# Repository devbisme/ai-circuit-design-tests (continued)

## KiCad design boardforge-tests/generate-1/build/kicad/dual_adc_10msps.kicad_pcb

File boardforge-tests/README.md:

# boardforge — tests

## Tool under test

[boardforge](https://github.com/devbisme/boardforge) turns a SKiDL circuit into a routed,
manufacturable KiCad board, headless. It has two parts:

- **A Python CLI, `boardforge`.** A project is a directory with a SKiDL file and a
  `boardforge.toml`. The CLI runs:
  - The physical pipeline (`run`, or one stage at a time): C1 `sch` (SKiDL → netlist →
    labels-only KiCad schematic via schematizer, SKiDL and KiCad ERC, netlist parity), C2
    `board`, C3 `place` (anchors, regions, FPGA/MCU pin swapping, compaction, a routability
    estimate), C4 `route` (Freerouting, then a built-in A*), C5 `check` (DRC, geometry
    checks, vendored kicad-happy 2.3.1 analyzers, thermal), C6 `fab` (JLCPCB Gerbers, BOM,
    CPL, schematic PDF, renders).
  - The B4 review gate (`review`): `constraints.json` checked against the design with
    ngspice path testbenches, rail-current budgets, datasheet absolute-max and power-pin
    checks, footprint-vs-datasheet package checks and a BOM diff.
  - A datasheet cache (`datasheets status | sync | add | check | show | publish | paths`),
    plus `render`, `status` and `doctor`.
- **A Claude Code plugin** (adapted from skidl-skills). `/new-circuit` drives seven phases:
  requirements (interview) → architecture and `constraints.json` (`circuit-architect`) →
  sourcing (`part-sourcer`) → datasheet extractions (`datasheet-librarian`) → SKiDL code
  (`skidl-coder`, or block coders plus `skidl-assembler`) → review (`erc-reviewer`) → board
  (the driver, using the CLI). There is an approval gate after each phase. Other skills:
  `design-review`, `erc-rules`, `find-part` (pcbparts MCP, with `skidl-part-search` as the
  fallback). Four hooks guard Bash calls, check written files, and print status at session
  start and stop.

The design-creating parts are `/new-circuit`, its agents, and `boardforge run`. The review
parts (`boardforge review`, `/design-review`, the C5 checks) all work on a boardforge SKiDL
project, not on an arbitrary KiCad design. So it is tested as a **generator** only.
Installation is described in [`setup.md`](setup.md).

- **Version:** boardforge 0.1.0 (PyPI). The plugin is 0.1.0 at commit 437b70d (2026-10-16),
  installed as `boardforge@devbisme-skills`.
- **Model:** Claude Opus 5.5 for the driver and the opus agents; Claude Sonnet 5.5 for
  `part-sourcer` (both set by the agents' frontmatter).
- **Claude Code version:** v2.1.302 (v2.1.301 at setup time).
- **Backend:** KiCad 10.0.4 (`~/bin/kicad10-root`: `kicad-cli` and the bundled Python 3.11
  `pcbnew`), SKiDL 3.0.0, schematizer 0.2.0, Freerouting 2.4.1, ngspice 44.2.

## Why this tool

<!-- TODO (author): drafted by Claude from the tool's description; replace with your own reasons. -->
- It is the successor to [skidl-skills](../skidl-skills-tests/), and it moves everything
  deterministic into a CLI: running the design, ERC, review gates, placement, routing and
  fab outputs. Agents only make decisions and call commands. The test is whether that
  lowers cost and gets further than skidl-skills, which stopped at a netlist.
- It covers the whole flow from prompt to fab files, with numeric review gates
  (`constraints.json` checked with ngspice) that the other generators don't have.

## Runs

| Run | What it tests | Prompts | Outcome | Equiv. API cost | Time |
|---|---|---|---|---|---|
| [`generate-1`](generate-1/) | A **full design** from the dual-ADC requirements | 1 ([`design_prompt.txt`](generate-1/design_prompt.txt)); no phase-gate approvals were needed (the prompt says not to pause) | 9-block SKiDL design → routed 4-layer 100 × 80 mm board, 239 parts. ERC 0 errors, netlist parity 217/217, review gate PASS, DRC 0 errors, release gate PASS. The C6 CPL dropped 80 parts (boardforge bug), fixed by hand | $23.89 | ~2 h 40 min wall clock (~8 min of it waiting out a session limit) |

### generate-1: full design

The prompt is [`design_prompt.txt`](generate-1/design_prompt.txt), identical to the one used
for the other tools' design runs (the dual-ADC prompt with the KiCad 10 path line).

Prompts, in sequence in one session:

```
create the design described in design-prompt.txt.
```

Claude invoked `/new-circuit` itself. Because the prompt says to choose options and not pause,
the driver ran phase 1 (requirements) without asking anything. Every requirement the prompt
didn't state is tagged `(driver)` in `SPEC.md`: 1 MΩ input, ±30 V protection, 1 MHz
passband, 4 layers, JLCPCB at qty 5. Each later approval gate was approved automatically.
One API session limit killed the datasheet agent partway through. The harness's "limit has
reset" message restarted the session, and the agent was resumed with its work intact.

Quick look:

- **Design:**
  - Signal path: BNC → 1 MΩ attenuator with a trimmer for probe compensation → BAV199
    clamp → OPA2810 buffer and two Sallen-Key stages → THS4551 FDA (MFB stage) → RC →
    ADS5231 (dual simultaneous 12-bit). The anti-alias filter has 7 poles: −80.9 dB at
    5 MHz nominal, −78.7 dB Monte-Carlo worst case (requirement ≥ 72 dB at fs/2).
  - Capture and link: XC6SLX9 Spartan-6 with a 16 MB W9812G6KH SDRAM (0.42 s at full rate)
    → FT232H sync FIFO → USB-C (USB 2.0 HS). W25Q32 config flash, JTAG and TRIG headers.
  - Power: 0.43 A worst case, so standard USB 2.0 power is enough; USB-C kept anyway.
    TLV62569 buck (3.3 V), TLV757 (1.2 V), LP5907 (3.3 V analog), LM27762 (±4 V).
  - 9 blocks (afe_channel instantiated twice), so the modular coding mode was used: 5 block
    work orders, then `skidl-assembler`.
- **Gates:**
  - Assembly first gave KiCad ERC 4 errors (missing power flags, J501 shield pin) and a BOM
    FAIL: none of the block coders set `LCSC` fields, though the rules require them.
  - One fix pass followed. It added the LCSC fields, 2 flags, the shield pin, and an R705
    pull-up for the LM27762 PGOOD pin; Claude added R705 to the BOM.
  - After that: SKiDL and KiCad ERC 0 errors, parity 217/217, `boardforge review` 43 PASS /
    0 FAIL / 13 NOT CHECKED, BOM PASS. `erc-reviewer` passed the design with 3 MEDIUM
    findings.
- **PCB (`boardforge run --from c2`):** 100 × 80 mm, 4 layers (In1 GND, In2 +3V3, GND pours
  on both outer layers).
  - Claude wrote the floorplan: 15 anchors, with the BNCs on the left edge, USB-C on the
    right, and the AFE → ADC → FPGA → FT232H chain left to right. One extra placement
    round anchored the USB ESD part U501, which C3 had put mid-board.
  - Routing took 11.4 min. Freerouting left 2 unrouted and 64 DRC errors; the A* router
    cleaned them up to 0/0.
  - DRC: 0 errors, 50 warnings (silkscreen 36, dangling stubs 9, hole-to-hole 5). Release
    gate PASS 12/12. 714 vias.
- **Not ready for fab:**
  - ADS5231 AVDD/VDRV abs-max is briefly exceeded at power-up (review W2; the fix is a
    one-net change, but it alters a block's signature). FT232H VREGIN sits at its 3.3 V
    minimum (W3).
  - ADS5231: single source, 152 in stock.
  - Facts that could not be verified:
    - The 12 MHz crystal has no datasheet.
    - The oscillator's jitter is unspecified.
    - The SDRAM facts come from the W9812G6JH datasheet.
  - The custom BNC and trimmer footprints have not been checked against their drawings.
  - No FPGA gateware, FT232H EEPROM image or host software.
- **boardforge problems found:**
  - **C6 CPL drops parts.**
    - Cause: `kicad-cli sch export bom` groups designators into ranges (`C1001-C1022`),
      and `_expand_designators` in the vendored `translate_bom_pnp.py` doesn't expand
      them. The CPL's BOM filter therefore silently dropped 80 of 239 parts.
    - Workaround: Claude regenerated the BOM and CPL in `build/fab/` with the ranges
      expanded, using boardforge's own adapter.
    - Fix: pass `--ref-range-delimiter ""` to the export call in `physical.py`.
    - Re-running `boardforge fab` brings the bug back.
  - **Review gate can't check a custom dual op-amp.** The SPICE path checks (GAIN and
    ALIAS, both HARD) report NOT CHECKED because boardforge can't map the OPA2810
    symbol's pin names (`VIN1+`, `VO1`) to op-amp roles, and `[review.models]` takes only
    one pin map per part. `erc-reviewer` re-ran the checker with the names mapped: 12/12
    pass (`build/reports/spice_patched/`).
  - **Stale stock data.** The `stock-check.py` mirror reported 7 in stock for the W25Q32;
    live stock was 12,414. The sourcer used pcbparts instead.
  - **Run-to-run netlist differences.** The symbol definitions of multi-unit parts list
    their pins in a different order on each run, so `diff` reports the netlists as
    different even though components and nets are identical.
  - **Other C4/C5 warnings:**
    - C4: fanout failed for 2 FPGA GND pads, and the copper cleanup was skipped because it
      would have disconnected 3 items.
    - C5: rail-current analysis doesn't recognise the LM27762's ±4 V outputs.
    - C6: 12 parts have CPL rotation offsets from an unverified table.
    - KiCad ERC: 258 `lib_symbol_mismatch` warnings.
  - **Agent behaviour:**
    - Block coders used two different conventions for power flags (`drive = POWER` vs
      `PWR_FLAG`), which caused 2 of the ERC errors.
    - The architect and sourcer returned receipts over the 10-line limit.

## Layout

```
boardforge-tests/
├── README.md                   <- this file
├── setup.md                    <- how boardforge was installed and configured
└── generate-1/                 <- run 1: full design from the dual-ADC prompt
    ├── .claude/settings.local.json  <- enables the plugin for this directory only
    ├── design_prompt.txt       <- the design prompt
    ├── claude_transcript.txt   <- session transcript (/export)
    ├── claude_cost.txt         <- token usage and equivalent API cost
    ├── session_cost.py         <- script that produces claude_cost.txt
    ├── executive_summary.md    <- what was done, results, risks
    ├── SPEC.md                 <- requirements, user vs. driver provenance
    ├── design_state.json       <- pipeline state written by the /new-circuit driver
    ├── handoffs/               <- one handoff per phase (and per block in 05_blocks/)
    ├── architecture/           <- block diagram, net plan, IC selection, risks, AFE SPICE deck
    ├── constraints.json        <- numeric review-gate constraints (ac_gain, rail_current)
    ├── sourcing/               <- sourced_bom.md / .csv
    ├── datasheets/             <- PDFs, extracted/*.json, *_SUMMARY.md
    ├── symbols/, footprints/   <- custom ADS5231/OPA2810 symbols, BNC and trimmer footprints
    ├── circuits/dual_adc_10msps/  <- SKiDL package: 9 block files + __main__.py
    ├── boardforge.toml         <- design, board and floorplan settings
    ├── review_report.md        <- erc-reviewer's phase 6 report
    └── build/                  <- kicad/ (schematic, board), reports/, renders/, fab/
```

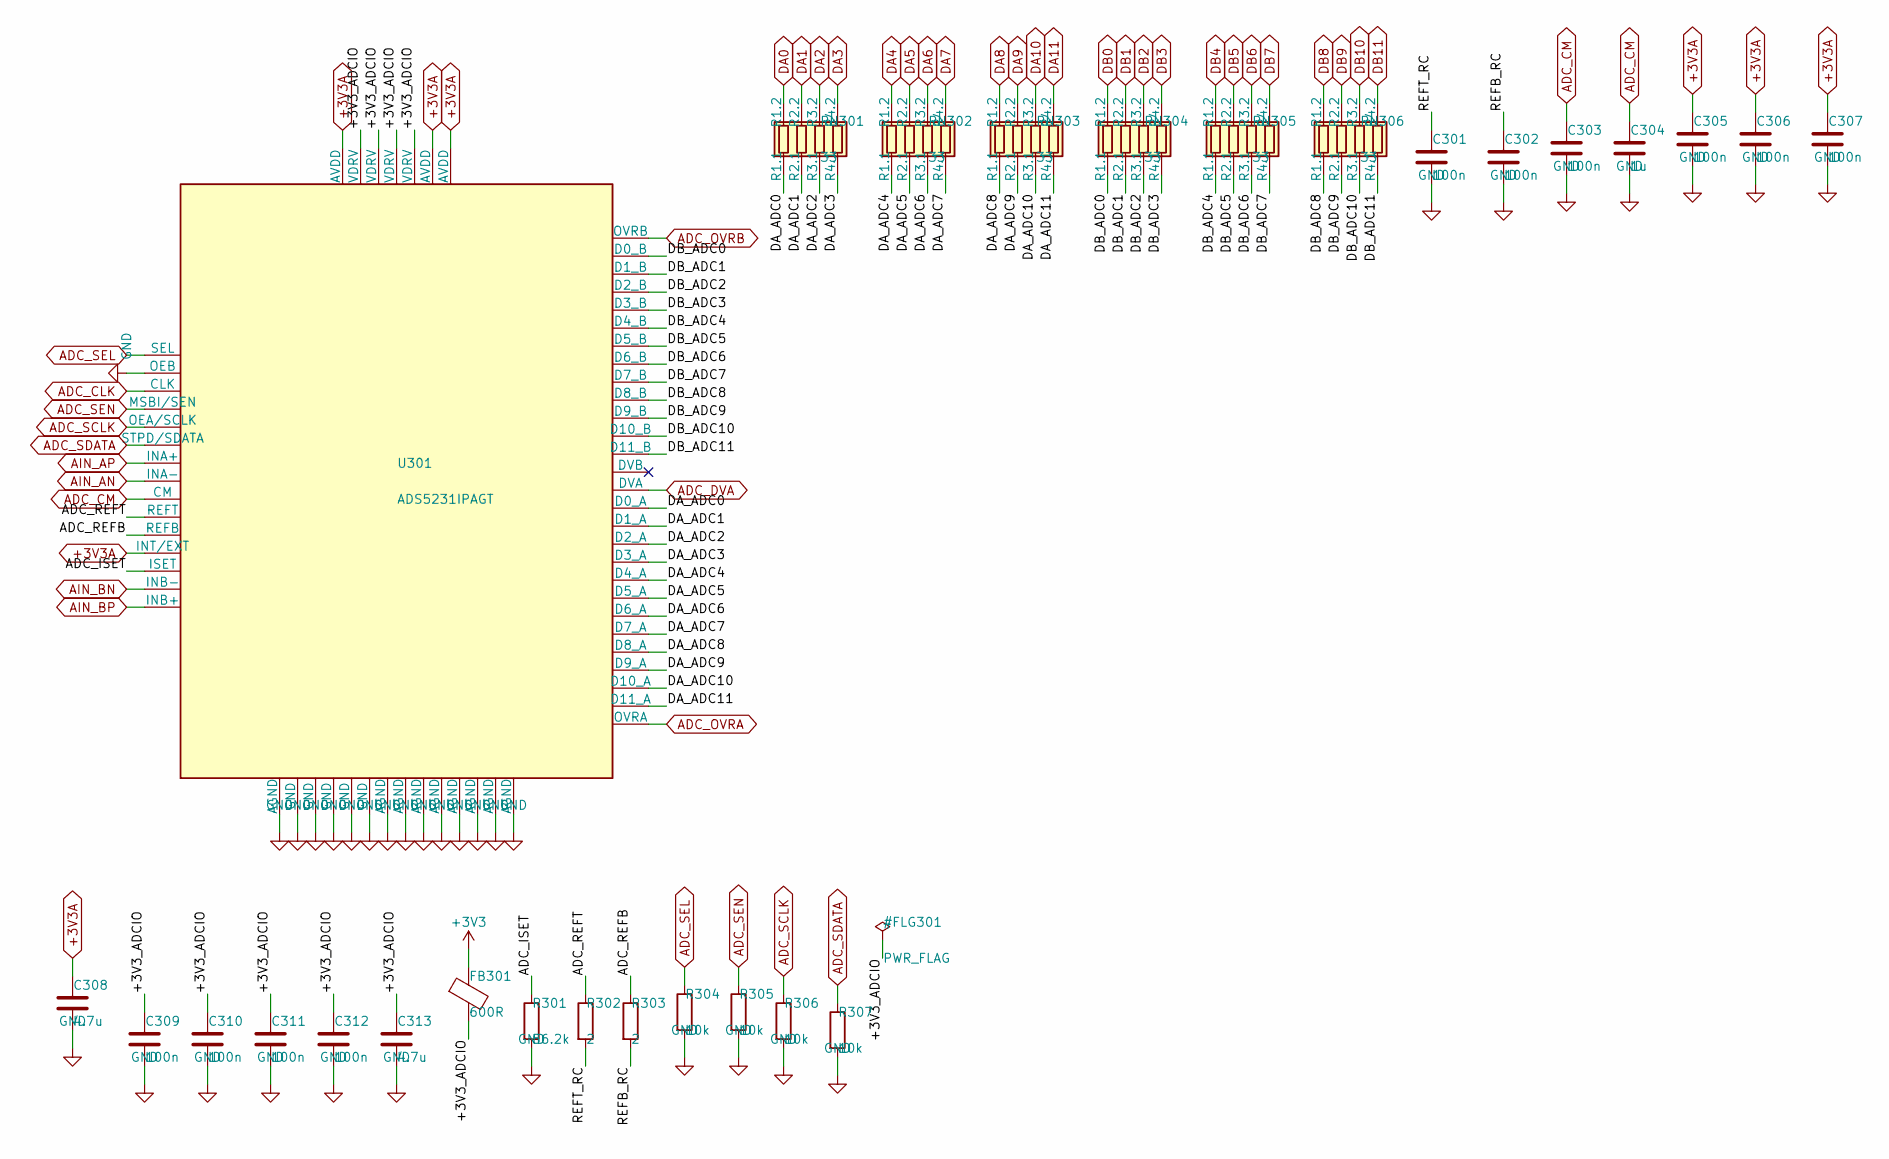
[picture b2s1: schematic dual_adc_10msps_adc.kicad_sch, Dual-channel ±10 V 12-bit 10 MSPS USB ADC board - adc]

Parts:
C301, C302, C303, C305, C306, C307, C309, C310, C311, C312: 100n; C_0402_1005Metric; MPN CL05B104KB54PNC; LCSC C307331
C304: 1u; C_0402_1005Metric; MPN CL05A105KA5NQNC; LCSC C52923
C308, C313: 4.7u; C_0603_1608Metric; MPN CL10A475KO8NNNC; LCSC C19666
FB301: 600R; L_0603_1608Metric; MPN BLM18KG601SN1D; LCSC C85833
R301: 56.2k; R_0402_1005Metric; MPN FRC0402F5622TS; LCSC C5126096
R302, R303: 2; R_0402_1005Metric; MPN FRC0402F2R00TS; LCSC C2998051
R304, R305, R306, R307: 10k; R_0402_1005Metric; MPN 0402WGF1002TCE; LCSC C25744
RN301, RN302, RN303, RN304, RN305, RN306: 33; R_Array_Convex_4x0402; MPN 4D02WGJ0330TCE; LCSC C25501
U301: ADS5231IPAGT; TQFP-64_10x10mm_P0.5mm; MPN ADS5231IPAGT; LCSC C2670079

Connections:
+3V3: FB301.1; also elsewhere on the board
+3V3A: C305.1, C306.1, C307.1, C308.1, U301.3 (AVDD), U301.46 (AVDD), U301.56 (INT/EXT), U301.57 (AVDD); also elsewhere on the board
/adc/+3V3_ADCIO: C309.1, C310.1, C311.1, C312.1, C313.1, FB301.2, U301.5 (VDRV), U301.8 (VDRV), U301.40 (VDRV), U301.43 (VDRV)
/adc/ADC_ISET: R301.1, U301.60 (ISET)
/adc/ADC_REFB: R303.1, U301.54 (REFB)
/adc/ADC_REFT: R302.1, U301.53 (REFT)
/adc/DA_ADC0: RN301.1 (R1.1), U301.27 (D0_A)
/adc/DA_ADC1: RN301.2 (R2.1), U301.28 (D1_A)
/adc/DA_ADC2: RN301.3 (R3.1), U301.29 (D2_A)
/adc/DA_ADC3: RN301.4 (R4.1), U301.30 (D3_A)
/adc/DA_ADC4: RN302.1 (R1.1), U301.31 (D4_A)
/adc/DA_ADC5: RN302.2 (R2.1), U301.32 (D5_A)
/adc/DA_ADC6: RN302.3 (R3.1), U301.33 (D6_A)
/adc/DA_ADC7: RN302.4 (R4.1), U301.34 (D7_A)
/adc/DA_ADC8: RN303.1 (R1.1), U301.35 (D8_A)
/adc/DA_ADC9: RN303.2 (R2.1), U301.36 (D9_A)
/adc/DA_ADC10: RN303.3 (R3.1), U301.37 (D10_A)
/adc/DA_ADC11: RN303.4 (R4.1), U301.38 (D11_A)
/adc/DB_ADC0: RN304.1 (R1.1), U301.10 (D0_B)
/adc/DB_ADC1: RN304.2 (R2.1), U301.11 (D1_B)
/adc/DB_ADC2: RN304.3 (R3.1), U301.12 (D2_B)
/adc/DB_ADC3: RN304.4 (R4.1), U301.13 (D3_B)
/adc/DB_ADC4: RN305.1 (R1.1), U301.14 (D4_B)
/adc/DB_ADC5: RN305.2 (R2.1), U301.15 (D5_B)
/adc/DB_ADC6: RN305.3 (R3.1), U301.16 (D6_B)
/adc/DB_ADC7: RN305.4 (R4.1), U301.17 (D7_B)
/adc/DB_ADC8: RN306.1 (R1.1), U301.18 (D8_B)
/adc/DB_ADC9: RN306.2 (R2.1), U301.19 (D9_B)
/adc/DB_ADC10: RN306.3 (R3.1), U301.20 (D10_B)
/adc/DB_ADC11: RN306.4 (R4.1), U301.21 (D11_B)
/adc/REFB_RC: C302.1, R303.2
/adc/REFT_RC: C301.1, R302.2
ADC_CLK: U301.24 (CLK); also elsewhere on the board
ADC_CM: C303.1, C304.1, U301.52 (CM); also elsewhere on the board
ADC_DVA: U301.26 (DVA); also elsewhere on the board
ADC_OVRA: U301.39 (OVRA); also elsewhere on the board
ADC_OVRB: U301.9 (OVRB); also elsewhere on the board
ADC_SCLK: R306.1, U301.42 (OEA/SCLK); also elsewhere on the board
ADC_SDATA: R307.1, U301.45 (STPD/SDATA); also elsewhere on the board
ADC_SEL: R304.1, U301.1 (SEL); also elsewhere on the board
ADC_SEN: R305.1, U301.41 (MSBI/SEN); also elsewhere on the board
AIN_AN: U301.51 (INA-); also elsewhere on the board
AIN_AP: U301.50 (INA+); also elsewhere on the board
AIN_BN: U301.62 (INB-); also elsewhere on the board
AIN_BP: U301.63 (INB+); also elsewhere on the board
DA0: RN301.8 (R1.2); also elsewhere on the board
DA1: RN301.7 (R2.2); also elsewhere on the board
DA2: RN301.6 (R3.2); also elsewhere on the board
DA3: RN301.5 (R4.2); also elsewhere on the board
DA4: RN302.8 (R1.2); also elsewhere on the board
DA5: RN302.7 (R2.2); also elsewhere on the board
DA6: RN302.6 (R3.2); also elsewhere on the board
DA7: RN302.5 (R4.2); also elsewhere on the board
DA8: RN303.8 (R1.2); also elsewhere on the board
DA9: RN303.7 (R2.2); also elsewhere on the board
DA10: RN303.6 (R3.2); also elsewhere on the board
DA11: RN303.5 (R4.2); also elsewhere on the board
DB0: RN304.8 (R1.2); also elsewhere on the board
DB1: RN304.7 (R2.2); also elsewhere on the board
DB2: RN304.6 (R3.2); also elsewhere on the board
DB3: RN304.5 (R4.2); also elsewhere on the board
DB4: RN305.8 (R1.2); also elsewhere on the board
DB5: RN305.7 (R2.2); also elsewhere on the board
DB6: RN305.6 (R3.2); also elsewhere on the board
DB7: RN305.5 (R4.2); also elsewhere on the board
DB8: RN306.8 (R1.2); also elsewhere on the board
DB9: RN306.7 (R2.2); also elsewhere on the board
DB10: RN306.6 (R3.2); also elsewhere on the board
DB11: RN306.5 (R4.2); also elsewhere on the board
GND: C301.2, C302.2, C303.2, C304.2, C305.2, C306.2, C307.2, C308.2, C309.2, C310.2, C311.2, C312.2, C313.2, R301.2, R304.2, R305.2, R306.2, R307.2, U301.2 (AGND), U301.4 (GND), U301.6 (OEB), U301.7 (GND), U301.23 (GND), U301.25 (GND), U301.44 (GND), U301.47 (AGND), U301.48 (AGND), U301.49 (AGND), U301.55 (AGND), U301.58 (AGND), U301.59 (AGND), U301.61 (AGND), U301.64 (AGND); also elsewhere on the board

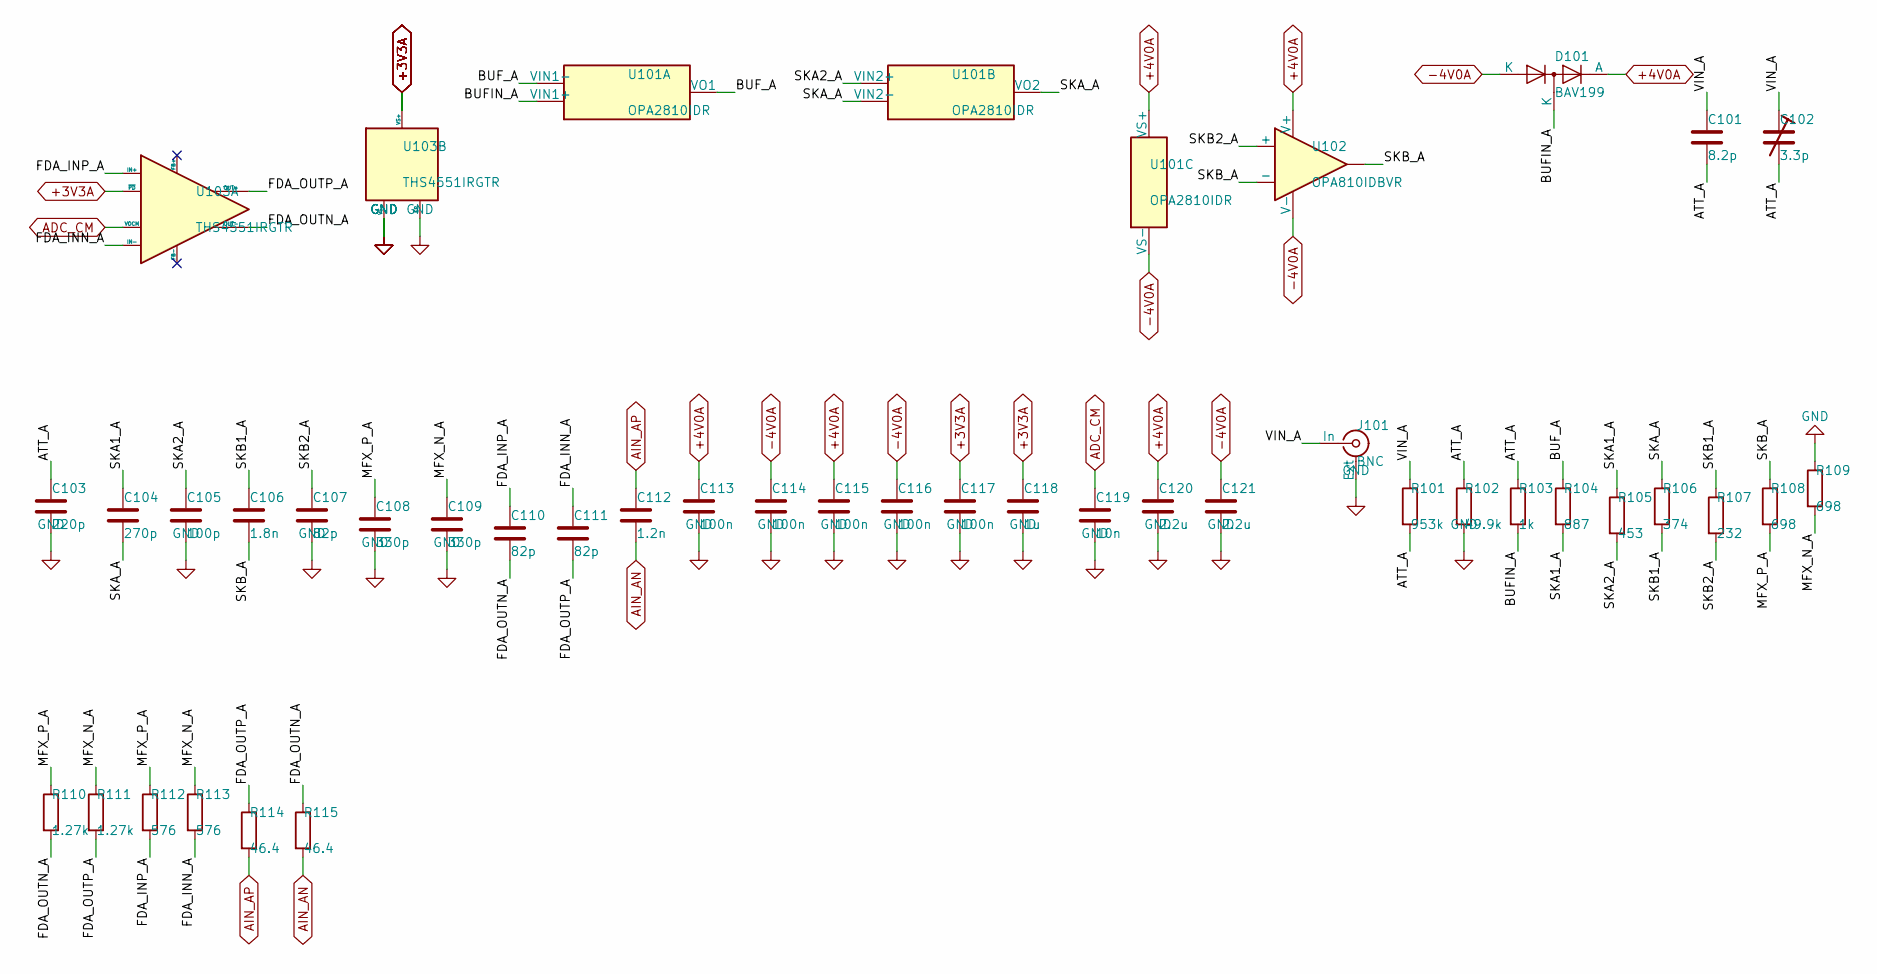
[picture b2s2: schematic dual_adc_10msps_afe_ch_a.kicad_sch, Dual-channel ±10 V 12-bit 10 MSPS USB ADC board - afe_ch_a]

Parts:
C101: 8.2p; C_0603_1608Metric; MPN GQM1875C2E8R2CB12D; LCSC C3874850
C102: 3.3p; C_Trimmer_SEHWA_STC3MA06; MPN STC3MA06-T1; LCSC C22468120
C103: 220p; C_0603_1608Metric; MPN GCM1885C2A221JA16D; LCSC C388907
C104: 270p; C_0402_1005Metric; MPN GRM1555C1H271GA01D; LCSC C161546
C105: 100p; C_0603_1608Metric; MPN 0603CG101G500NT; LCSC C182932
C106: 1.8n; C_0603_1608Metric; MPN GRM1885C1H182FA01D; LCSC C882525
C107, C110, C111: 82p; C_0603_1608Metric; MPN GQM1875C2E820GB12D; LCSC C2171259
C108, C109: 330p; C_0402_1005Metric; MPN GRM1555C1H331GA01D; LCSC C237507
C112: 1.2n; C_0603_1608Metric; MPN GCM1885C1H122FA16D; LCSC C1517816
C113, C114, C115, C116, C117: 100n; C_0402_1005Metric; MPN CL05B104KB54PNC; LCSC C307331
C118: 1u; C_0402_1005Metric; MPN CL05A105KA5NQNC; LCSC C52923
C119: 10n; C_0402_1005Metric; MPN CL05B103KB5NNNC; LCSC C15195
C120, C121: 2.2u; C_0603_1608Metric; MPN CL10A225KO8NNNC; LCSC C23630
D101: BAV199; SOT-23; MPN BAV199; LCSC C68971
J101: BNC; BNC_KH-BNC50-3511; MPN KH-BNC50-3511; LCSC C2837587
R101: 953k; R_1206_3216Metric; MPN WR12X9533FTL; LCSC C368327
R102: 49.9k; R_0603_1608Metric; MPN 0603WAF4992T5E; LCSC C23184
R103: 1k; R_0603_1608Metric; MPN 0603WAF1001T5E; LCSC C21190
R104: 887; R_0402_1005Metric; MPN CRCW0402887RFKED; LCSC C4012675
R105: 453; R_0402_1005Metric; MPN FRC0402F4530TS; LCSC C5126227
R106: 374; R_0402_1005Metric; MPN RMS04FT3740; LCSC C208875
R107: 232; R_0402_1005Metric; MPN GR0402F232RTAG00; LCSC C49655645
R108, R109: 698; R_0402_1005Metric; MPN GR0402F698RTAG00; LCSC C49655034
R110, R111: 1.27k; R_0402_1005Metric; MPN FRC0402F1271TS; LCSC C3013151
R112, R113: 576; R_0402_1005Metric; MPN 0402WGF5760TCE; LCSC C45320
R114, R115: 46.4; R_0402_1005Metric; MPN RC0402FR-0746R4L; LCSC C273734
U101: OPA2810IDR; SOIC-8_3.9x4.9mm_P1.27mm; MPN OPA2810IDR; LCSC C1849413
U102: OPA810IDBVR; SOT-23-5; MPN OPA810IDBVR; LCSC C2833513
U103: THS4551IRGTR; VQFN-16-1EP_3x3mm_P0.5mm_EP1.68x1.68mm; MPN THS4551IRGTR; LCSC C2869590

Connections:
+3V3A: C117.1, C118.1, U103.5 (VS+), U103.6 (VS+), U103.7 (VS+), U103.8 (VS+), U103.12 (~PD); also elsewhere on the board
+4V0A: C113.1, C115.1, C120.1, D101.2 (A), U101.8 (VS+), U102.5 (V+); also elsewhere on the board
-4V0A: C114.1, C116.1, C121.1, D101.1 (K), U101.4 (VS-), U102.2 (V-); also elsewhere on the board
/afe_ch_a/ATT_A: C101.2, C102.2, C103.1, R101.2, R102.1, R103.1
/afe_ch_a/BUFIN_A: D101.3 (K), R103.2, U101.3 (VIN1+)
/afe_ch_a/BUF_A: R104.1, U101.1 (VO1), U101.2 (VIN1-)
/afe_ch_a/FDA_INN_A: C111.1, R113.2, U103.3 (IN-)
/afe_ch_a/FDA_INP_A: C110.1, R112.2, U103.2 (IN+)
/afe_ch_a/FDA_OUTN_A: C110.2, R110.2, R115.1, U103.11 (OUT-)
/afe_ch_a/FDA_OUTP_A: C111.2, R111.2, R114.1, U103.10 (OUT+)
/afe_ch_a/MFX_N_A: C109.1, R109.2, R111.1, R113.1
/afe_ch_a/MFX_P_A: C108.1, R108.2, R110.1, R112.1
/afe_ch_a/SKA1_A: C104.1, R104.2, R105.1
/afe_ch_a/SKA2_A: C105.1, R105.2, U101.5 (VIN2+)
/afe_ch_a/SKA_A: C104.2, R106.1, U101.6 (VIN2-), U101.7 (VO2)
/afe_ch_a/SKB1_A: C106.1, R106.2, R107.1
/afe_ch_a/SKB2_A: C107.1, R107.2, U102.3 (+)
/afe_ch_a/SKB_A: C106.2, R108.1, U102.1, U102.4 (-)
/afe_ch_a/VIN_A: C101.1, C102.1, J101.1 (In), R101.1
ADC_CM: C119.1, U103.9 (VOCM); also elsewhere on the board
AIN_AN: C112.2, R115.2; also elsewhere on the board
AIN_AP: C112.1, R114.2; also elsewhere on the board
GND: C103.2, C105.2, C107.2, C108.2, C109.2, C113.2, C114.2, C115.2, C116.2, C117.2, C118.2, C119.2, C120.2, C121.2, J101.2 (Ext), R102.2, R109.1, U103.13 (VS-), U103.14 (VS-), U103.15 (VS-), U103.16 (VS-), U103.17 (EP); also elsewhere on the board

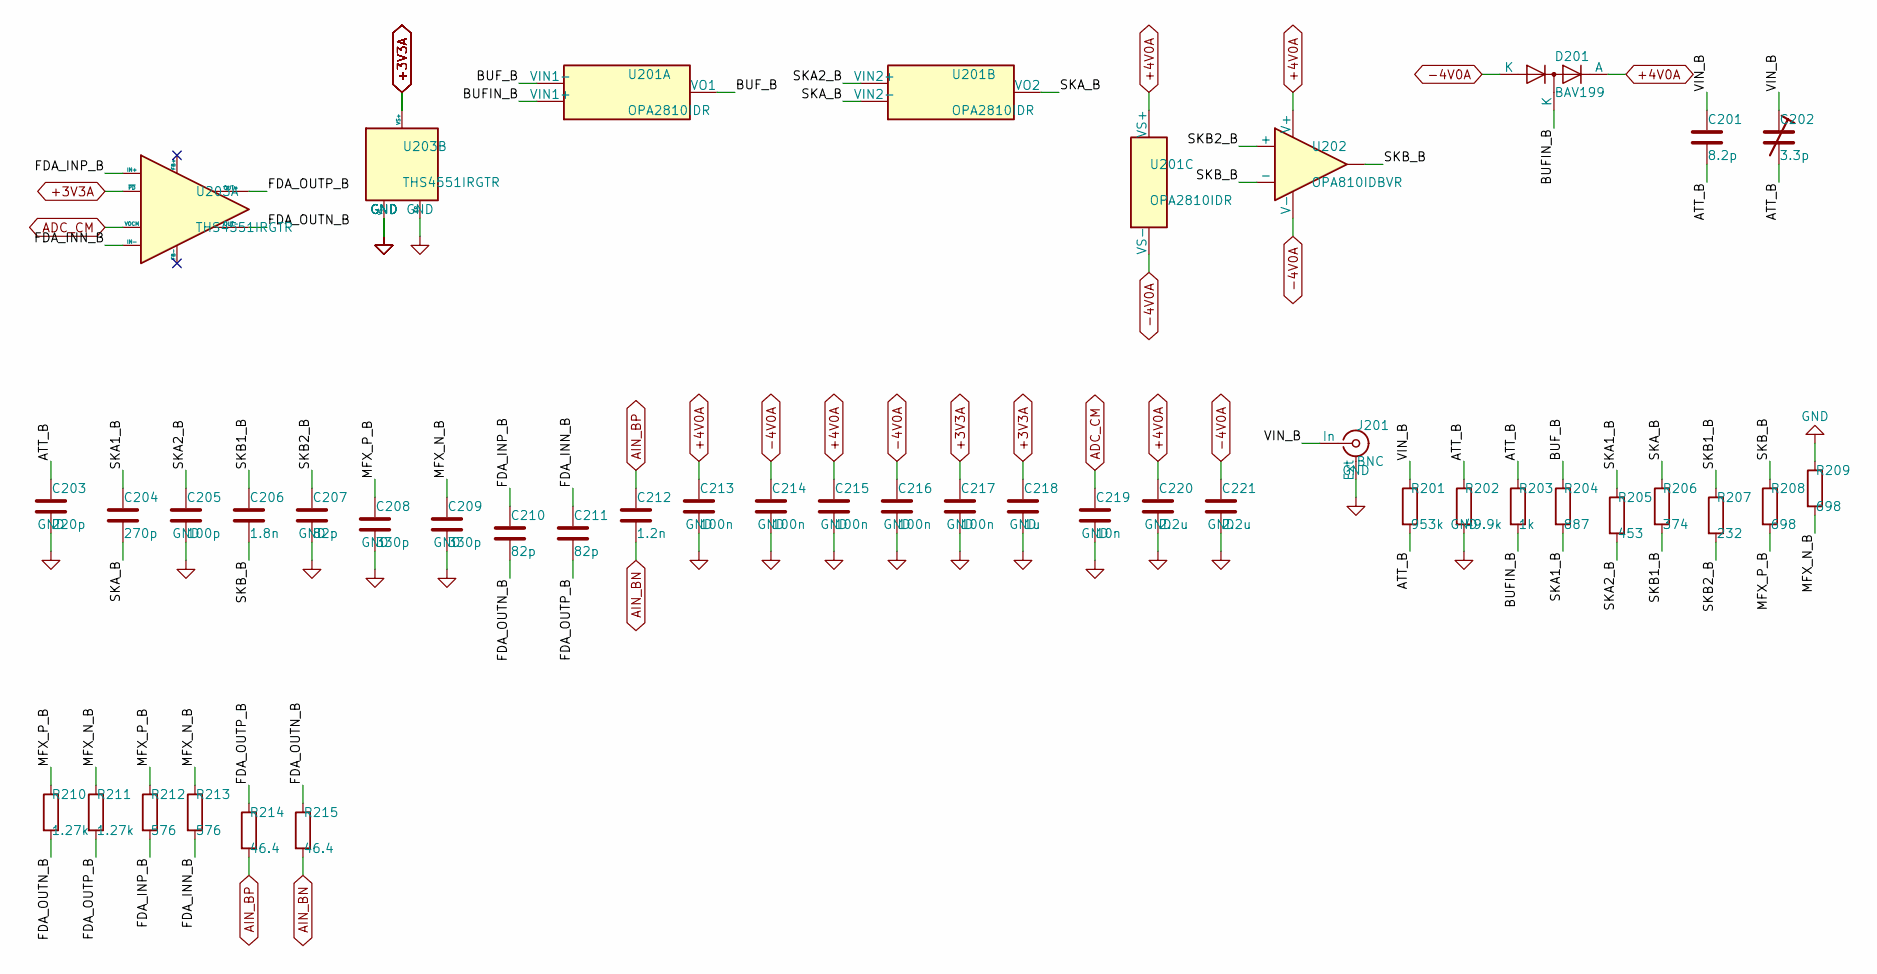
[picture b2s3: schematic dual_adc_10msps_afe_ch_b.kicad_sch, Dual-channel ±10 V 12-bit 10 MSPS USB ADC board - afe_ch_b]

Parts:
C201: 8.2p; C_0603_1608Metric; MPN GQM1875C2E8R2CB12D; LCSC C3874850
C202: 3.3p; C_Trimmer_SEHWA_STC3MA06; MPN STC3MA06-T1; LCSC C22468120
C203: 220p; C_0603_1608Metric; MPN GCM1885C2A221JA16D; LCSC C388907
C204: 270p; C_0402_1005Metric; MPN GRM1555C1H271GA01D; LCSC C161546
C205: 100p; C_0603_1608Metric; MPN 0603CG101G500NT; LCSC C182932
C206: 1.8n; C_0603_1608Metric; MPN GRM1885C1H182FA01D; LCSC C882525
C207, C210, C211: 82p; C_0603_1608Metric; MPN GQM1875C2E820GB12D; LCSC C2171259
C208, C209: 330p; C_0402_1005Metric; MPN GRM1555C1H331GA01D; LCSC C237507
C212: 1.2n; C_0603_1608Metric; MPN GCM1885C1H122FA16D; LCSC C1517816
C213, C214, C215, C216, C217: 100n; C_0402_1005Metric; MPN CL05B104KB54PNC; LCSC C307331
C218: 1u; C_0402_1005Metric; MPN CL05A105KA5NQNC; LCSC C52923
C219: 10n; C_0402_1005Metric; MPN CL05B103KB5NNNC; LCSC C15195
C220, C221: 2.2u; C_0603_1608Metric; MPN CL10A225KO8NNNC; LCSC C23630
D201: BAV199; SOT-23; MPN BAV199; LCSC C68971
J201: BNC; BNC_KH-BNC50-3511; MPN KH-BNC50-3511; LCSC C2837587
R201: 953k; R_1206_3216Metric; MPN WR12X9533FTL; LCSC C368327
R202: 49.9k; R_0603_1608Metric; MPN 0603WAF4992T5E; LCSC C23184
R203: 1k; R_0603_1608Metric; MPN 0603WAF1001T5E; LCSC C21190
R204: 887; R_0402_1005Metric; MPN CRCW0402887RFKED; LCSC C4012675
R205: 453; R_0402_1005Metric; MPN FRC0402F4530TS; LCSC C5126227
R206: 374; R_0402_1005Metric; MPN RMS04FT3740; LCSC C208875
R207: 232; R_0402_1005Metric; MPN GR0402F232RTAG00; LCSC C49655645
R208, R209: 698; R_0402_1005Metric; MPN GR0402F698RTAG00; LCSC C49655034
R210, R211: 1.27k; R_0402_1005Metric; MPN FRC0402F1271TS; LCSC C3013151
R212, R213: 576; R_0402_1005Metric; MPN 0402WGF5760TCE; LCSC C45320
R214, R215: 46.4; R_0402_1005Metric; MPN RC0402FR-0746R4L; LCSC C273734
U201: OPA2810IDR; SOIC-8_3.9x4.9mm_P1.27mm; MPN OPA2810IDR; LCSC C1849413
U202: OPA810IDBVR; SOT-23-5; MPN OPA810IDBVR; LCSC C2833513
U203: THS4551IRGTR; VQFN-16-1EP_3x3mm_P0.5mm_EP1.68x1.68mm; MPN THS4551IRGTR; LCSC C2869590

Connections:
+3V3A: C217.1, C218.1, U203.5 (VS+), U203.6 (VS+), U203.7 (VS+), U203.8 (VS+), U203.12 (~PD); also elsewhere on the board
+4V0A: C213.1, C215.1, C220.1, D201.2 (A), U201.8 (VS+), U202.5 (V+); also elsewhere on the board
-4V0A: C214.1, C216.1, C221.1, D201.1 (K), U201.4 (VS-), U202.2 (V-); also elsewhere on the board
/afe_ch_b/ATT_B: C201.2, C202.2, C203.1, R201.2, R202.1, R203.1
/afe_ch_b/BUFIN_B: D201.3 (K), R203.2, U201.3 (VIN1+)
/afe_ch_b/BUF_B: R204.1, U201.1 (VO1), U201.2 (VIN1-)
/afe_ch_b/FDA_INN_B: C211.1, R213.2, U203.3 (IN-)
/afe_ch_b/FDA_INP_B: C210.1, R212.2, U203.2 (IN+)
/afe_ch_b/FDA_OUTN_B: C210.2, R210.2, R215.1, U203.11 (OUT-)
/afe_ch_b/FDA_OUTP_B: C211.2, R211.2, R214.1, U203.10 (OUT+)
/afe_ch_b/MFX_N_B: C209.1, R209.2, R211.1, R213.1
/afe_ch_b/MFX_P_B: C208.1, R208.2, R210.1, R212.1
/afe_ch_b/SKA1_B: C204.1, R204.2, R205.1
/afe_ch_b/SKA2_B: C205.1, R205.2, U201.5 (VIN2+)
/afe_ch_b/SKA_B: C204.2, R206.1, U201.6 (VIN2-), U201.7 (VO2)
/afe_ch_b/SKB1_B: C206.1, R206.2, R207.1
/afe_ch_b/SKB2_B: C207.1, R207.2, U202.3 (+)
/afe_ch_b/SKB_B: C206.2, R208.1, U202.1, U202.4 (-)
/afe_ch_b/VIN_B: C201.1, C202.1, J201.1 (In), R201.1
ADC_CM: C219.1, U203.9 (VOCM); also elsewhere on the board
AIN_BN: C212.2, R215.2; also elsewhere on the board
AIN_BP: C212.1, R214.2; also elsewhere on the board
GND: C203.2, C205.2, C207.2, C208.2, C209.2, C213.2, C214.2, C215.2, C216.2, C217.2, C218.2, C219.2, C220.2, C221.2, J201.2 (Ext), R202.2, R209.1, U203.13 (VS-), U203.14 (VS-), U203.15 (VS-), U203.16 (VS-), U203.17 (EP); also elsewhere on the board

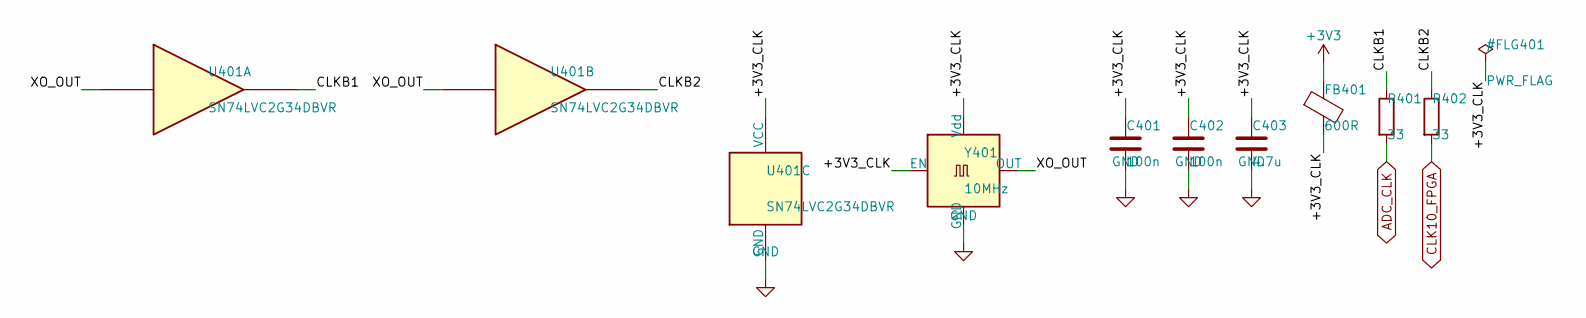
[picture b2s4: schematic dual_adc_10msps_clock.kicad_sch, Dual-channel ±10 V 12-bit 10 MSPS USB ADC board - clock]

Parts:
C401, C402: 100n; C_0402_1005Metric; MPN CL05B104KB54PNC; LCSC C307331
C403: 4.7u; C_0603_1608Metric; MPN CL10A475KO8NNNC; LCSC C19666
FB401: 600R; L_0603_1608Metric; MPN BLM18KG601SN1D; LCSC C85833
R401, R402: 33; R_0402_1005Metric; MPN 0402WGF330JTCE; LCSC C25105
U401: SN74LVC2G34DBVR; SOT-23-6; MPN SN74LVC2G34DBVR; LCSC C7394039
Y401: 10MHz; Oscillator_SMD_Abracon_ASE-4Pin_3.2x2.5mm; MPN SX3M10.000B10F20TNN; LCSC C5452682

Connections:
+3V3: FB401.1; also elsewhere on the board
/clock/+3V3_CLK: C401.1, C402.1, C403.1, FB401.2, U401.5 (VCC), Y401.1 (EN), Y401.4 (Vdd)
/clock/CLKB1: R401.1, U401.6
/clock/CLKB2: R402.1, U401.4
/clock/XO_OUT: U401.1, U401.3, Y401.3 (OUT)
ADC_CLK: R401.2; also elsewhere on the board
CLK10_FPGA: R402.2; also elsewhere on the board
GND: C401.2, C402.2, C403.2, U401.2 (GND), Y401.2 (GND); also elsewhere on the board
